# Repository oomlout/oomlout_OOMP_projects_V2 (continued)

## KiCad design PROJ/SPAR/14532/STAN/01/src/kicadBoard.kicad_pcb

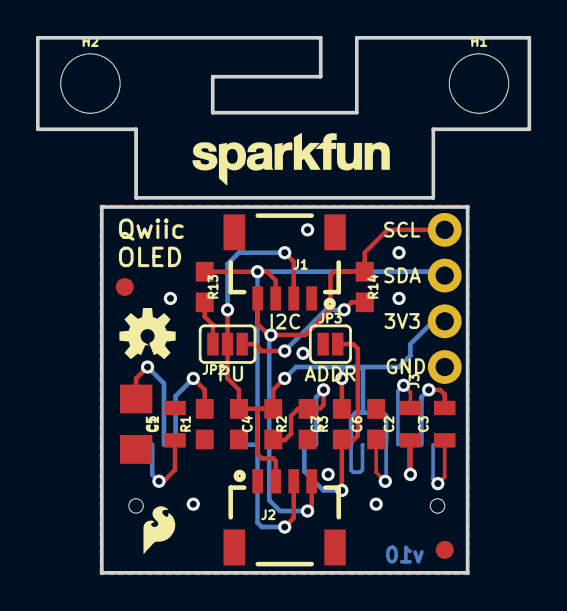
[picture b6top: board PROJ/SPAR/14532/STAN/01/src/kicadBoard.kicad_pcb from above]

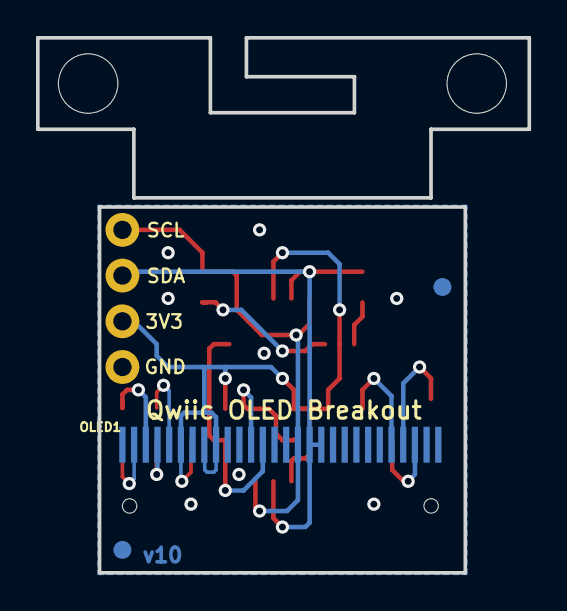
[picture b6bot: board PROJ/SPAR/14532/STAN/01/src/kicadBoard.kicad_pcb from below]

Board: 2 copper layers, 27.3 x 29.7 mm, 29 parts (3 on the bottom side), 15 nets.

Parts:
C1: 2.2uF; 0805
C2, C3: 1.0uF; 0805
C4, C6, C7: 1.0uF; 0603
C5: 4.7uF; 1206
FID1, FID2, FID3, FID4: FIDUCIAL1X2; FIDUCIAL-1X2
FRAME1: FRAME-LETTER; CREATIVE_COMMONS
H1, H2: STAND-OFF
J1, J2: 1X04_1MM_RA
J3: 1X04_NO_SILK
JP2: SMT-JUMPER_3_2-NC_PASTE_SILK
JP3: SMT-JUMPER_2_NO_SILK
LOGO1: REVISION
LOGO2: SFE_LOGO_FLAME.1_INCH; SFE_LOGO_FLAME_.1
LOGO3: OSHW-LOGOS; OSHW-LOGO-S
LOGO4: SFE_LOGO_NAME.1_INCH; SFE_LOGO_NAME_.1
OLED1: OLED0.66; OLED-0.66-64X48
R1: 390k; 0603
R2, R3: 10k; 0603
R13, R14: 4.7k; 0603

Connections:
C1P: C2.1, OLED1.4
C2N: C3.2, OLED1.3
D0/SCK: J1.4, J2.4, J3.4, OLED1.16, R14.1
D1/MOSI: J1.3, J2.3, J3.3, OLED1.17, OLED1.18, R13.1
D/C: JP3.2, OLED1.13, R3.1
GND: C1.2, C4.2, C5.2, C6.2, C7.2, J1.1, J2.1, J3.1, JP3.1, OLED1.1, OLED1.7, OLED1.10, OLED1.27, OLED1.28, R1.1
IREF: OLED1.24, R1.2
unnamed: C3.1, OLED1.2
unnamed: C2.2, OLED1.5
unnamed: JP2.3, R13.2
unnamed: JP2.1, R14.2
RESET: C7.1, OLED1.12, R2.2
VCC: C1.1, OLED1.26
VCOMH: C5.1, OLED1.25
VDD: C4.1, C6.1, J1.2, J2.2, J3.2, JP2.2, OLED1.6, OLED1.8, OLED1.9, R2.1, R3.2

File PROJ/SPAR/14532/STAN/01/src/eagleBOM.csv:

"Part";"Value";"Device";"Package";"Description";"PROD_ID";"VALUE";
"C1";"2.2uF";"2.2UF-0805-25V-(+80/-20%)";"0805";"2.2µF ceramic capacitors";"CAP-11624";"2.2uF";
"C2";"1.0uF";"1.0UF-0805-25V-10%";"0805";"1µF ceramic capacitors";"CAP-08064";"1.0uF";
"C3";"1.0uF";"1.0UF-0805-25V-10%";"0805";"1µF ceramic capacitors";"CAP-08064";"1.0uF";
"C4";"1.0uF";"1.0UF-0603-16V-10%";"0603";"1µF ceramic capacitors";"CAP-00868";"1.0uF";
"C5";"4.7uF";"4.7UF-1206-16V-(+80/-20%)";"1206";"4.7µF ceramic capacitors";"CAP-10300";"4.7uF";
"C6";"1.0uF";"1.0UF-0603-16V-10%";"0603";"1µF ceramic capacitors";"CAP-00868";"1.0uF";
"C7";"1.0uF";"1.0UF-0603-16V-10%";"0603";"1µF ceramic capacitors";"CAP-00868";"1.0uF";
"FID1";"FIDUCIAL1X2";"FIDUCIAL1X2";"FIDUCIAL-1X2";"Fiducial Alignment Points";"";"";
"FID2";"FIDUCIAL1X2";"FIDUCIAL1X2";"FIDUCIAL-1X2";"Fiducial Alignment Points";"";"";
"FID3";"FIDUCIAL1X2";"FIDUCIAL1X2";"FIDUCIAL-1X2";"Fiducial Alignment Points";"";"";
"FID4";"FIDUCIAL1X2";"FIDUCIAL1X2";"FIDUCIAL-1X2";"Fiducial Alignment Points";"";"";
"FRAME1";"FRAME-LETTER";"FRAME-LETTER";"CREATIVE_COMMONS";"Schematic Frame";"";"";
"H1";"STAND-OFF";"STAND-OFF";"STAND-OFF";"Stand Off";"";"";
"H2";"STAND-OFF";"STAND-OFF";"STAND-OFF";"Stand Off";"";"";
"J1";"";"QWIIC_CONNECTORJS-1MM";"1X04_1MM_RA";"SparkFun I2C Standard Qwiic Connector";"CONN-13694";"";
"J2";"";"QWIIC_CONNECTORJS-1MM";"1X04_1MM_RA";"SparkFun I2C Standard Qwiic Connector";"CONN-13694";"";
"J3";"";"I2C_STANDARD_NO_SILK";"1X04_NO_SILK";"SparkFun I2C Standard Pinout Header";"";"";
"JP2";"";"JUMPER-SMT_3_2-NC_PASTE_SILK";"SMT-JUMPER_3_2-NC_PASTE_SILK";"Normally closed solder jumper (2 of 2 connections)";"";"";
"JP3";"";"JUMPER-SMT_2_NO_SILK";"SMT-JUMPER_2_NO_SILK";"Normally open jumper";"";"";
"LOGO1";"REVISION";"REVISION";"REVISION";""Revision By" Text";"";"";
"LOGO2";"SFE_LOGO_FLAME.1_INCH";"SFE_LOGO_FLAME.1_INCH";"SFE_LOGO_FLAME_.1";"SparkFun Flame Logo";"";"";
"LOGO3";"OSHW-LOGOS";"OSHW-LOGOS";"OSHW-LOGO-S";"Open Source Hardware Logo This logo indicates the piece of hardware it is found on incorporates a OSHW license and/or adheres to the definition of open source hardware found here: http://freedomdefined.org/OSHW";"";"";
"LOGO4";"SFE_LOGO_NAME.1_INCH";"SFE_LOGO_NAME.1_INCH";"SFE_LOGO_NAME_.1";"SparkFun Font Logo";"";"";
"OLED1";"OLED0.66";"OLED0.66";"OLED-0.66-64X48";"Micro OLED";"LCD-12019";"";
"R1";"390k";"390KOHM-0603-1/10W-1%";"0603";"390kΩ resistor";"RES-12024";"390k";
"R2";"10k";"10KOHM-0603-1/10W-1%";"0603";"10kΩ resistor";"RES-00824";"10k";
"R3";"10k";"10KOHM-0603-1/10W-1%";"0603";"10kΩ resistor";"RES-00824";"10k";
"R13";"4.7k";"4.7KOHM-0603-1/10W-1%";"0603";"4.7kΩ resistor";"RES-07857";"4.7k";
"R14";"4.7k";"4.7KOHM-0603-1/10W-1%";"0603";"4.7kΩ resistor";"RES-07857";"4.7k";

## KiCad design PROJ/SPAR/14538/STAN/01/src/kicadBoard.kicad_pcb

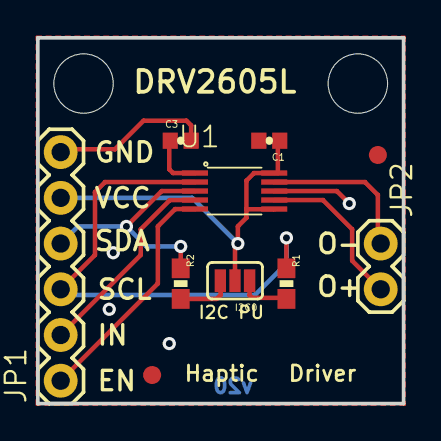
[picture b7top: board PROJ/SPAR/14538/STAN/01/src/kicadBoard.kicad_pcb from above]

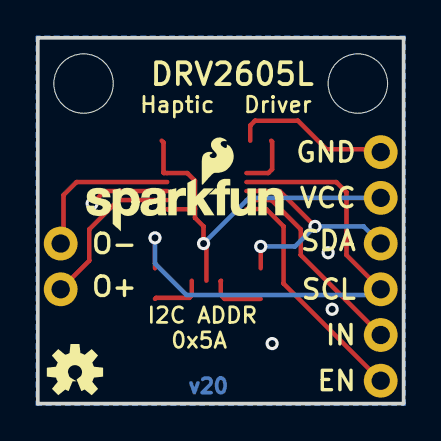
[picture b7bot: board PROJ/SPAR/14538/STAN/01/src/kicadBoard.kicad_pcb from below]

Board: 2 copper layers, 20.3 x 20.3 mm, 15 parts (2 on the bottom side), 11 nets.

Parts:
C1, C3: 1.0uF; 0402-CAP
FID1, FID2: FIDUCIAL1X2; FIDUCIAL-1X2
FRAME2: FRAME-LETTER; CREATIVE_COMMONS
I2C0: JUMPER-PAD-3-NC_BY_PASTE; PAD-JUMPER-3-NC_BY_PASTE_YES_SILK_FULL_BOX
JP1: 1X06
JP2: 1X02
LOGO2: OSHW-LOGOS; OSHW-LOGO-S
LOGO4: SFE_LOGO_NAME_FLAME.1_INCH; SFE_LOGO_NAME_FLAME_.1
R1, R2: 2.2k; 0603-RES
STANDOFF1, STANDOFF4: STAND-OFF
U1: DRV2605L; VSSOP-10

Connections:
GND: C1.2, C3.2, JP1.6, U1.P$8
unnamed: JP1.4, R2.1, U1.P$3
unnamed: JP1.3, R1.1, U1.P$2
unnamed: C3.1, U1.P$1
unnamed: JP1.2, U1.P$4
unnamed: JP1.1, U1.P$5
unnamed: JP2.1, U1.P$9
unnamed: JP2.2, U1.P$7
unnamed: I2C0.3, R2.2
unnamed: I2C0.1, R1.2
VCC: C1.1, I2C0.2, JP1.5, U1.P$6, U1.P$10

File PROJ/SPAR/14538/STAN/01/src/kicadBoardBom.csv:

"Id";"Designator";"Package";"Quantity";"Designation";"Supplier and ref";
1;"FID2,FID1";"FIDUCIAL-1X2";2;"FIDUCIAL1X2";;;
2;"R2,R1";"0603-RES";2;"2.2k";;;
3;"C1,C3";"0402-CAP";2;"1.0uF";;;
4;"I2C0";"PAD-JUMPER-3-NC_BY_PASTE_YES_SILK_FULL_BOX";1;"JUMPER-PAD-3-NC_BY_PASTE";;;
5;"U1";"VSSOP-10";1;"DRV2605L";;;
6;"STANDOFF1,STANDOFF4";"STAND-OFF";2;"STAND-OFF";;;
7;"JP2";"1X02";1;"";;;
8;"FRAME2";"CREATIVE_COMMONS";1;"FRAME-LETTER";;;
9;"JP1";"1X06";1;"";;;
10;"LOGO2";"OSHW-LOGO-S";1;"OSHW-LOGOS";;;
11;"LOGO4";"SFE_LOGO_NAME_FLAME_.1";1;"SFE_LOGO_NAME_FLAME.1_INCH";;;

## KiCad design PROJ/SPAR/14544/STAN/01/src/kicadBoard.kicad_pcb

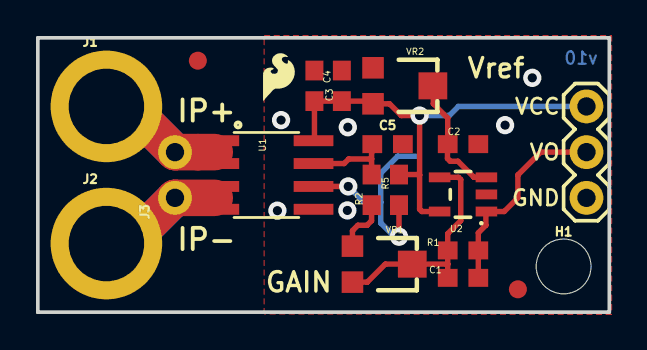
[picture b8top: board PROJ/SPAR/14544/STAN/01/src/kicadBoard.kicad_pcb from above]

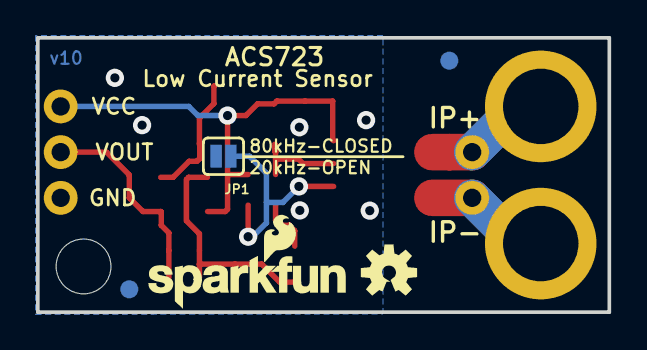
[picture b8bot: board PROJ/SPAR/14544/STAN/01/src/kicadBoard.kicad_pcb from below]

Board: 2 copper layers, 31.8 x 15.2 mm, 26 parts (5 on the bottom side), 10 nets.

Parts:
C1: 100pF; 0603
C2, C3, C4: 0.1uF; 0603
C5: 1nF; 0603
FD1, FD2, FD3, FD4: FIDUCIAL1X2; FIDUCIAL-1X2
FRAME1: FRAME-LETTER; CREATIVE_COMMONS
H1: STAND-OFFTIGHT; STAND-OFF-TIGHT
J1, J2: SMTSO-256-ET-0.165DIA
J3: 1X02_NO_SILK
JP1: JUMPER-SMT_2_NO_SILK; SMT-JUMPER_2_NO_SILK
JP3: 1X03
LOGO1: SFE_LOGO_NAME_FLAME.1_INCH; SFE_LOGO_NAME_FLAME_.1
LOGO2: OSHW-LOGOS; OSHW-LOGO-S
LOGO3: SFE_LOGO_FLAME.1_INCH; SFE_LOGO_FLAME_.1
R1: 22k; 0603
R2: 1k; 0603
R5: 4.7k; 0603
U1: ACS723; SO08
U2: OPA344; SOT23-5
VR1, VR2: 10k; TRIMPOT-SMD-TC33X

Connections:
5V: C3.1, C4.2, JP3.1, R5.2, U1.8, U2.5, VR2.3
BW_SEL: JP1.2, R5.1, U1.6
GND: C2.2, C3.2, C4.1, C5.2, JP1.1, JP3.3, U1.5, U2.2, VR2.1
IP+: J1.P$1, J3.2, U1.1, U1.2
IP-: J2.P$1, J3.1, U1.3, U1.4
unnamed: R2.1, VR1.1
unnamed: C1.2, R1.2, U2.4, VR1.2, VR1.3
unnamed: C2.1, U2.3, VR2.2
VIOUT: C5.1, R2.2, U1.7
VO: C1.1, JP3.2, R1.1, U2.1

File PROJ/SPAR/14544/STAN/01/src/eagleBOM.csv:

"Part";"Value";"Device";"Package";"Description";"PART_#";"PROD_ID";"VALUE";
"C1";"100pF";"100PF-0603-50V-5%";"0603";"100pF/0.1nF ceramic capacitors";"";"CAP-07883";"100pF";
"C2";"0.1uF";"0.1UF-0603-25V-(+80/-20%)";"0603";"0.1µF ceramic capacitors";"";"CAP-00810";"0.1uF";
"C3";"0.1uF";"0.1UF-0603-25V-(+80/-20%)";"0603";"0.1µF ceramic capacitors";"";"CAP-00810";"0.1uF";
"C4";"0.1uF";"0.1UF-0603-25V-(+80/-20%)";"0603";"0.1µF ceramic capacitors";"";"CAP-00810";"0.1uF";
"C5";"1nF";"1.0NF/1000PF-0603-50V-10%";"0603";"1nF/1,000pF ceramic capacitors";"";"CAP-07886";"1nF";
"FD1";"FIDUCIAL1X2";"FIDUCIAL1X2";"FIDUCIAL-1X2";"Fiducial Alignment Points";"";"";"";
"FD2";"FIDUCIAL1X2";"FIDUCIAL1X2";"FIDUCIAL-1X2";"Fiducial Alignment Points";"";"";"";
"FD3";"FIDUCIAL1X2";"FIDUCIAL1X2";"FIDUCIAL-1X2";"Fiducial Alignment Points";"";"";"";
"FD4";"FIDUCIAL1X2";"FIDUCIAL1X2";"FIDUCIAL-1X2";"Fiducial Alignment Points";"";"";"";
"FRAME1";"FRAME-LETTER";"FRAME-LETTER";"CREATIVE_COMMONS";"Schematic Frame - Letter";"";"";"";
"H1";"STAND-OFFTIGHT";"STAND-OFFTIGHT";"STAND-OFF-TIGHT";"Stand Off";"";"";"";
"J1";"";"CONN_01SMTSO-256-ET-0.165DIA";"SMTSO-256-ET-0.165DIA";"Single connection point. Often used as Generic Header-pin footprint for 0.1 inch spaced/style header connections";"";"HW-08694";"";
"J2";"";"CONN_01SMTSO-256-ET-0.165DIA";"SMTSO-256-ET-0.165DIA";"Single connection point. Often used as Generic Header-pin footprint for 0.1 inch spaced/style header connections";"";"HW-08694";"";
"J3";"";"CONN_021X02_NO_SILK";"1X02_NO_SILK";"Multi connection point. Often used as Generic Header-pin footprint for 0.1 inch spaced/style header connections";"";"";"";
"JP1";"JUMPER-SMT_2_NO_SILK";"JUMPER-SMT_2_NO_SILK";"SMT-JUMPER_2_NO_SILK";"Normally open jumper";"";"";"";
"JP3";"";"M03PTH";"1X03";"Header 3";"";"";"";
"LOGO1";"SFE_LOGO_NAME_FLAME.1_INCH";"SFE_LOGO_NAME_FLAME.1_INCH";"SFE_LOGO_NAME_FLAME_.1";"SparkFun Font Logo w/ Flame";"";"";"";
"LOGO2";"OSHW-LOGOS";"OSHW-LOGOS";"OSHW-LOGO-S";"Open-Source Hardware (OSHW) Logo";"";"";"";
"LOGO3";"SFE_LOGO_FLAME.1_INCH";"SFE_LOGO_FLAME.1_INCH";"SFE_LOGO_FLAME_.1";"SparkFun Flame Logo";"";"";"";
"R1";"22k";"22KOHM-0603-1/10W-1%";"0603";"22kΩ resistor";"";"RES-07853";"22k";
"R2";"1k";"1KOHM-0603-1/10W-1%";"0603";"1kΩ resistor";"";"RES-07856";"1k";
"R5";"4.7k";"4.7KOHM-0603-1/10W-1%";"0603";"4.7kΩ resistor";"";"RES-07857";"4.7k";
"U1";"ACS723";"ACS723";"SO08";"";"ACS723ACS723LLCTR-05AB-T2";"IC-13872";"";
"U2";"OPA344";"OPA344";"SOT23-5";"Single gate rail-to-rail output op-amp. Inputs extend 300mV past rails.";"";"IC-08251";"OPA344";
"VR1";"10k";"TRIMPOT-SMD-3MM-OPEN-1/10W-25%";"TRIMPOT-SMD-TC33X";"Trimming Potentiometer (Trimpot)";"";"RES-12428, RES-08048";"10k";
"VR2";"10k";"TRIMPOT-SMD-3MM-OPEN-1/10W-25%";"TRIMPOT-SMD-TC33X";"Trimming Potentiometer (Trimpot)";"";"RES-12428, RES-08048";"10k";
